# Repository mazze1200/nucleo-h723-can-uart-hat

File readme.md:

# CAN and UART hat for STM32 Nucleo H723ZG eval board

# FTDI Sub-D 
Pin 1 = TXD / PIN16
Pin 6 = RXD / PIN17
Pin 3 = GND

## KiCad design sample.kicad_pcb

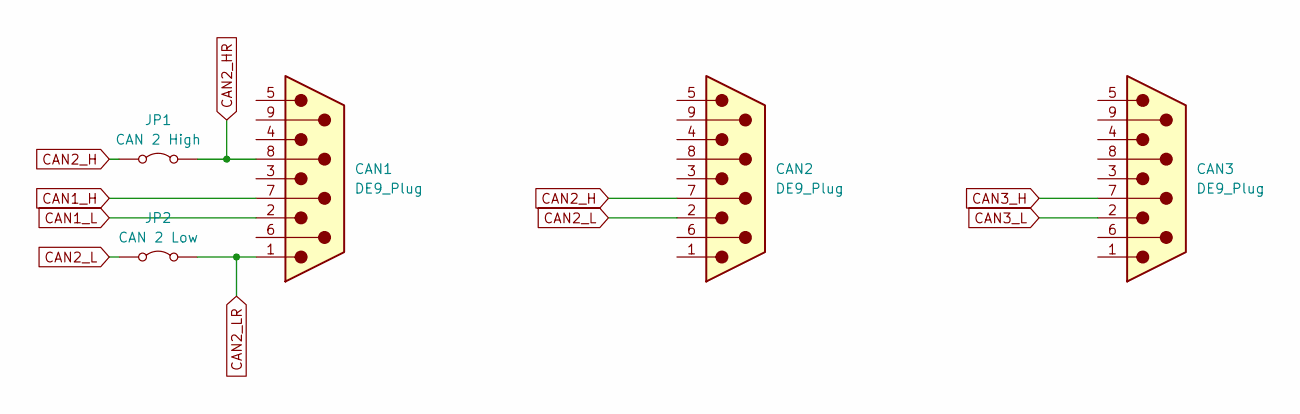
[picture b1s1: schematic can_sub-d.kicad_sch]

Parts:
CAN1, CAN2, CAN3: DE9_Plug; DSUB-9_Female_Horizontal_P2.77x2.54mm_EdgePinOffset9.40mm
JP1: CAN 2 High; TestPoint_2Pads_Pitch2.54mm_Drill0.8mm
JP2: CAN 2 Low; TestPoint_2Pads_Pitch2.54mm_Drill0.8mm

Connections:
CAN1_H: CAN1.7; also elsewhere on the board
CAN1_L: CAN1.2; also elsewhere on the board
CAN2_H: CAN2.7, JP1.1 (A); also elsewhere on the board
CAN2_HR: CAN1.8, JP1.2 (B)
CAN2_L: CAN2.2, JP2.1 (A); also elsewhere on the board
CAN2_LR: CAN1.1, JP2.2 (B)
CAN3_H: CAN3.7; also elsewhere on the board
CAN3_L: CAN3.2; also elsewhere on the board

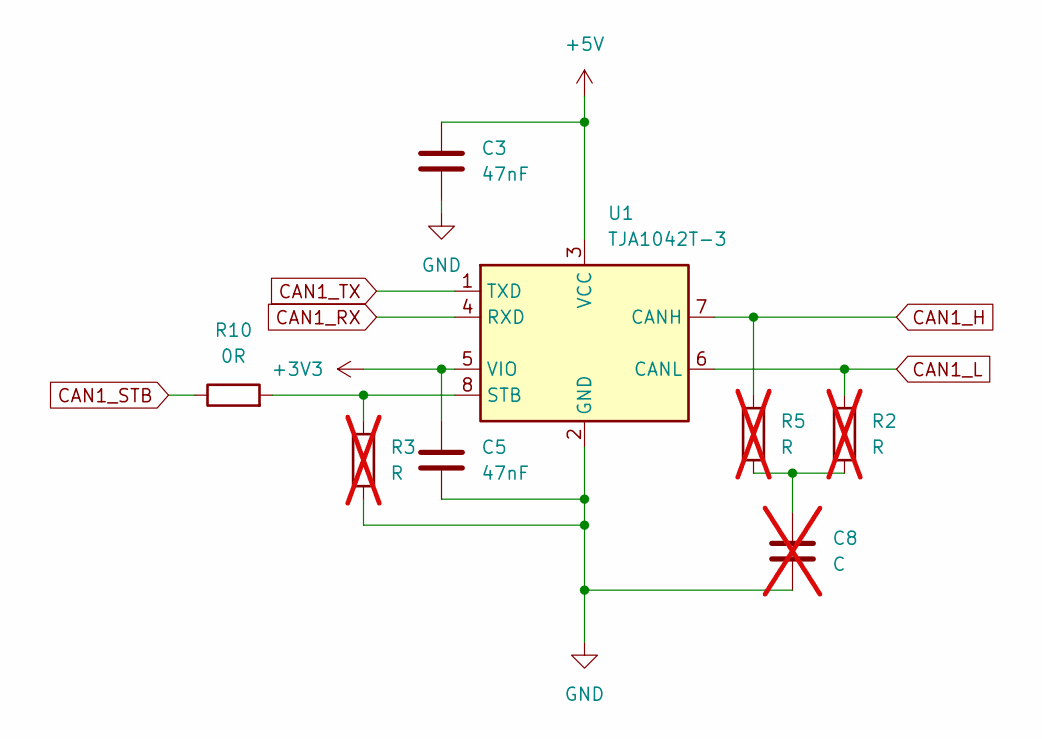
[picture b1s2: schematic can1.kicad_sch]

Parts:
C3, C5: 47nF; C_1206_3216Metric_Pad1.33x1.80mm_HandSolder
C8: C; C_1206_3216Metric_Pad1.33x1.80mm_HandSolder; not fitted
R2, R3, R5: R; R_1206_3216Metric_Pad1.30x1.75mm_HandSolder; not fitted
R10: 0R; R_1206_3216Metric_Pad1.30x1.75mm_HandSolder
U1: TJA1042T-3; SOIC-8_3.9x4.9mm_P1.27mm

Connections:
+3V3: C5.1, U1.5 (VIO); also elsewhere on the board
+5V: C3.1, U1.3 (VCC); also elsewhere on the board
CAN1_H: R5.1, U1.7 (CANH); also elsewhere on the board
CAN1_L: R2.1, U1.6 (CANL); also elsewhere on the board
CAN1_RX: U1.4 (RXD); also elsewhere on the board
CAN1_STB: R10.1; also elsewhere on the board
CAN1_TX: U1.1 (TXD); also elsewhere on the board
GND: C3.2, C5.2, C8.2, R3.2, U1.2 (GND); also elsewhere on the board
unnamed: C8.1, R2.2, R5.2
unnamed: R3.1, R10.2, U1.8 (STB)

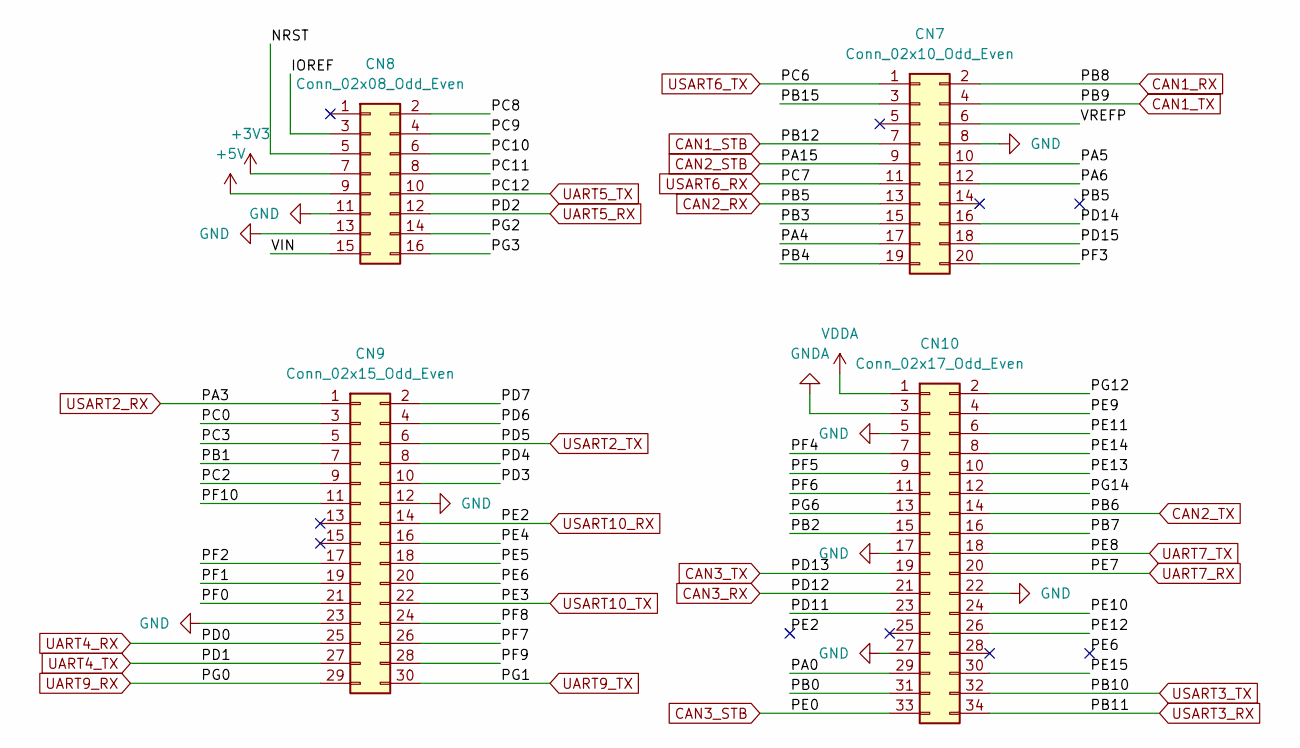
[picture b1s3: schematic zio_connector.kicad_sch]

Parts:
CN7: Conn_02x10_Odd_Even; PinHeader_2x10_P2.54mm_Vertical
CN8: Conn_02x08_Odd_Even; PinHeader_2x08_P2.54mm_Vertical
CN9: Conn_02x15_Odd_Even; PinHeader_2x15_P2.54mm_Vertical
CN10: Conn_02x17_Odd_Even; PinHeader_2x17_P2.54mm_Vertical

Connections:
+3V3: CN8.7; also elsewhere on the board
+5V: CN8.9; also elsewhere on the board
/ZIO Connector/IOREF: CN8.3
/ZIO Connector/NRST: CN8.5
/ZIO Connector/PA0: CN10.29
/ZIO Connector/PA4: CN7.17
/ZIO Connector/PA5: CN7.10
/ZIO Connector/PA6: CN7.12
/ZIO Connector/PB0: CN10.31
/ZIO Connector/PB1: CN9.7
/ZIO Connector/PB2: CN10.15
/ZIO Connector/PB3: CN7.15
/ZIO Connector/PB4: CN7.19
/ZIO Connector/PB7: CN10.16
/ZIO Connector/PB15: CN7.3
/ZIO Connector/PC0: CN9.3
/ZIO Connector/PC2: CN9.9
/ZIO Connector/PC3: CN9.5
/ZIO Connector/PC8: CN8.2
/ZIO Connector/PC9: CN8.4
/ZIO Connector/PC10: CN8.6
/ZIO Connector/PC11: CN8.8
/ZIO Connector/PD3: CN9.10
/ZIO Connector/PD4: CN9.8
/ZIO Connector/PD6: CN9.4
/ZIO Connector/PD7: CN9.2
/ZIO Connector/PD11: CN10.23
/ZIO Connector/PD14: CN7.16
/ZIO Connector/PD15: CN7.18
/ZIO Connector/PE4: CN9.16
/ZIO Connector/PE5: CN9.18
/ZIO Connector/PE6: CN9.20
/ZIO Connector/PE9: CN10.4
/ZIO Connector/PE10: CN10.24
/ZIO Connector/PE11: CN10.6
/ZIO Connector/PE12: CN10.26
/ZIO Connector/PE13: CN10.10
/ZIO Connector/PE14: CN10.8
/ZIO Connector/PE15: CN10.30
/ZIO Connector/PF0: CN9.21
/ZIO Connector/PF1: CN9.19
/ZIO Connector/PF2: CN9.17
/ZIO Connector/PF3: CN7.20
/ZIO Connector/PF4: CN10.7
/ZIO Connector/PF5: CN10.9
/ZIO Connector/PF6: CN10.11
/ZIO Connector/PF7: CN9.26
/ZIO Connector/PF8: CN9.24
/ZIO Connector/PF9: CN9.28
/ZIO Connector/PF10: CN9.11
/ZIO Connector/PG2: CN8.14
/ZIO Connector/PG3: CN8.16
/ZIO Connector/PG6: CN10.13
/ZIO Connector/PG12: CN10.2
/ZIO Connector/PG14: CN10.12
/ZIO Connector/VIN: CN8.15
/ZIO Connector/VREFP: CN7.6
CAN1_RX: CN7.2; also elsewhere on the board
CAN1_STB: CN7.7; also elsewhere on the board
CAN1_TX: CN7.4; also elsewhere on the board
CAN2_RX: CN7.13; also elsewhere on the board
CAN2_STB: CN7.9; also elsewhere on the board
CAN2_TX: CN10.14; also elsewhere on the board
CAN3_RX: CN10.21; also elsewhere on the board
CAN3_STB: CN10.33; also elsewhere on the board
CAN3_TX: CN10.19; also elsewhere on the board
GND: CN7.8, CN8.11, CN8.13, CN9.12, CN9.23, CN10.5, CN10.17, CN10.22, CN10.27; also elsewhere on the board
GNDA: CN10.3
UART4_RX: CN9.25; also elsewhere on the board
UART4_TX: CN9.27; also elsewhere on the board
UART5_RX: CN8.12; also elsewhere on the board
UART5_TX: CN8.10; also elsewhere on the board
UART7_RX: CN10.20; also elsewhere on the board
UART7_TX: CN10.18; also elsewhere on the board
UART9_RX: CN9.29; also elsewhere on the board
UART9_TX: CN9.30; also elsewhere on the board
USART2_RX: CN9.1; also elsewhere on the board
USART2_TX: CN9.6; also elsewhere on the board
USART3_RX: CN10.34; also elsewhere on the board
USART3_TX: CN10.32; also elsewhere on the board
USART6_RX: CN7.11; also elsewhere on the board
USART6_TX: CN7.1; also elsewhere on the board
USART10_RX: CN9.14; also elsewhere on the board
USART10_TX: CN9.22; also elsewhere on the board
VDDA: CN10.1

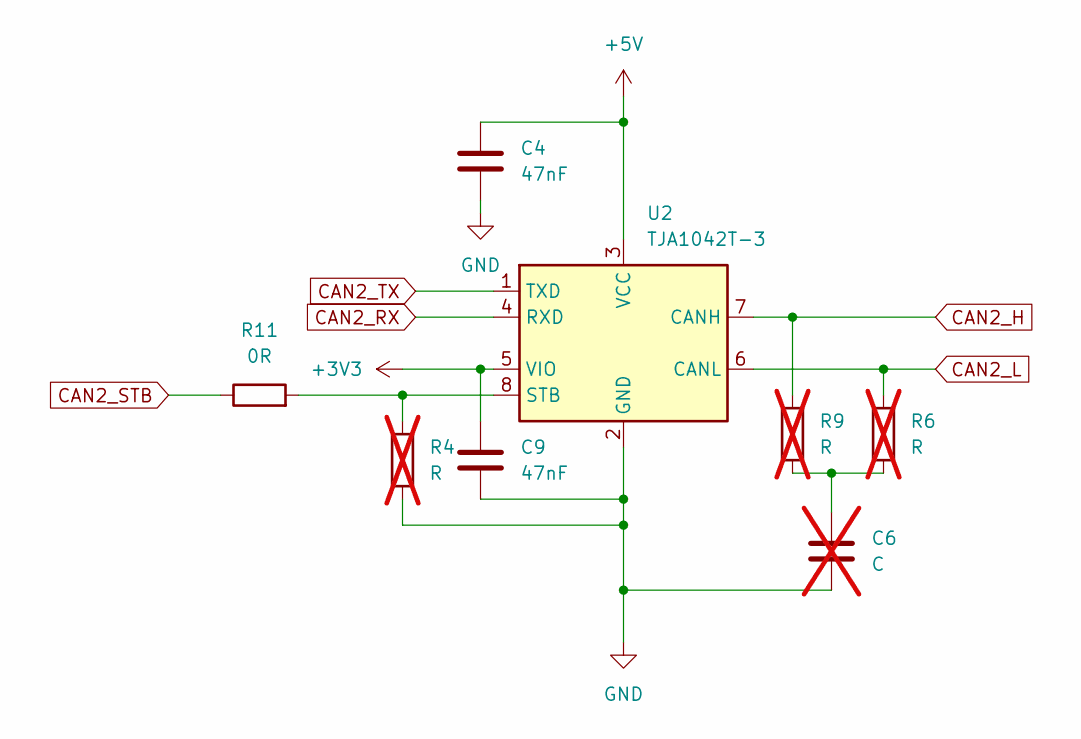
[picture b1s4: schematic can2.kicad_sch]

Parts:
C4, C9: 47nF; C_1206_3216Metric_Pad1.33x1.80mm_HandSolder
C6: C; C_1206_3216Metric_Pad1.33x1.80mm_HandSolder; not fitted
R4, R6, R9: R; R_1206_3216Metric_Pad1.30x1.75mm_HandSolder; not fitted
R11: 0R; R_1206_3216Metric_Pad1.30x1.75mm_HandSolder
U2: TJA1042T-3; SOIC-8_3.9x4.9mm_P1.27mm

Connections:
+3V3: C9.1, U2.5 (VIO); also elsewhere on the board
+5V: C4.1, U2.3 (VCC); also elsewhere on the board
CAN2_H: R9.1, U2.7 (CANH); also elsewhere on the board
CAN2_L: R6.1, U2.6 (CANL); also elsewhere on the board
CAN2_RX: U2.4 (RXD); also elsewhere on the board
CAN2_STB: R11.1; also elsewhere on the board
CAN2_TX: U2.1 (TXD); also elsewhere on the board
GND: C4.2, C6.2, C9.2, R4.2, U2.2 (GND); also elsewhere on the board
unnamed: C6.1, R6.2, R9.2
unnamed: R4.1, R11.2, U2.8 (STB)

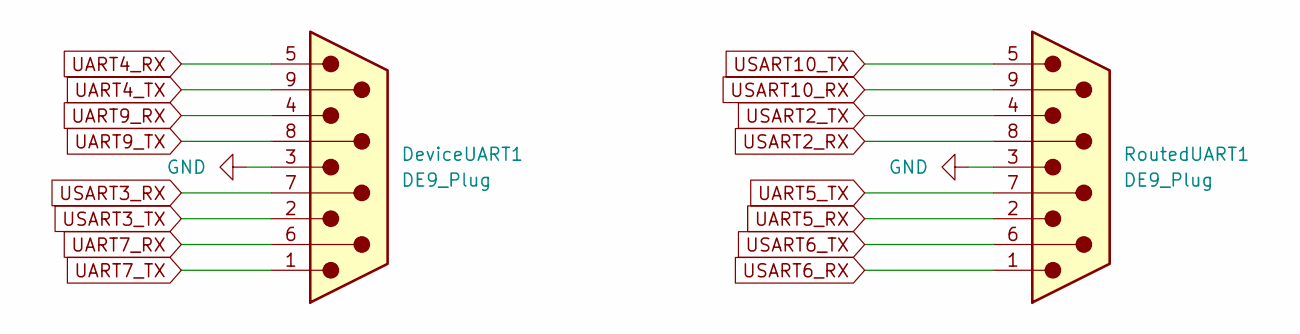
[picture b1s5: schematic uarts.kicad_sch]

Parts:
DeviceUART1: DE9_Plug; DSUB-9_Female_Horizontal_P2.77x2.54mm_EdgePinOffset9.40mm
RoutedUART1: DE9_Plug; DSUB-9_Male_Horizontal_P2.77x2.54mm_EdgePinOffset9.40mm

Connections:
GND: DeviceUART1.3, RoutedUART1.3; also elsewhere on the board
UART4_RX: DeviceUART1.5; also elsewhere on the board
UART4_TX: DeviceUART1.9; also elsewhere on the board
UART5_RX: RoutedUART1.2; also elsewhere on the board
UART5_TX: RoutedUART1.7; also elsewhere on the board
UART7_RX: DeviceUART1.6; also elsewhere on the board
UART7_TX: DeviceUART1.1; also elsewhere on the board
UART9_RX: DeviceUART1.4; also elsewhere on the board
UART9_TX: DeviceUART1.8; also elsewhere on the board
USART2_RX: RoutedUART1.8; also elsewhere on the board
USART2_TX: RoutedUART1.4; also elsewhere on the board
USART3_RX: DeviceUART1.7; also elsewhere on the board
USART3_TX: DeviceUART1.2; also elsewhere on the board
USART6_RX: RoutedUART1.1; also elsewhere on the board
USART6_TX: RoutedUART1.6; also elsewhere on the board
USART10_RX: RoutedUART1.9; also elsewhere on the board
USART10_TX: RoutedUART1.5; also elsewhere on the board

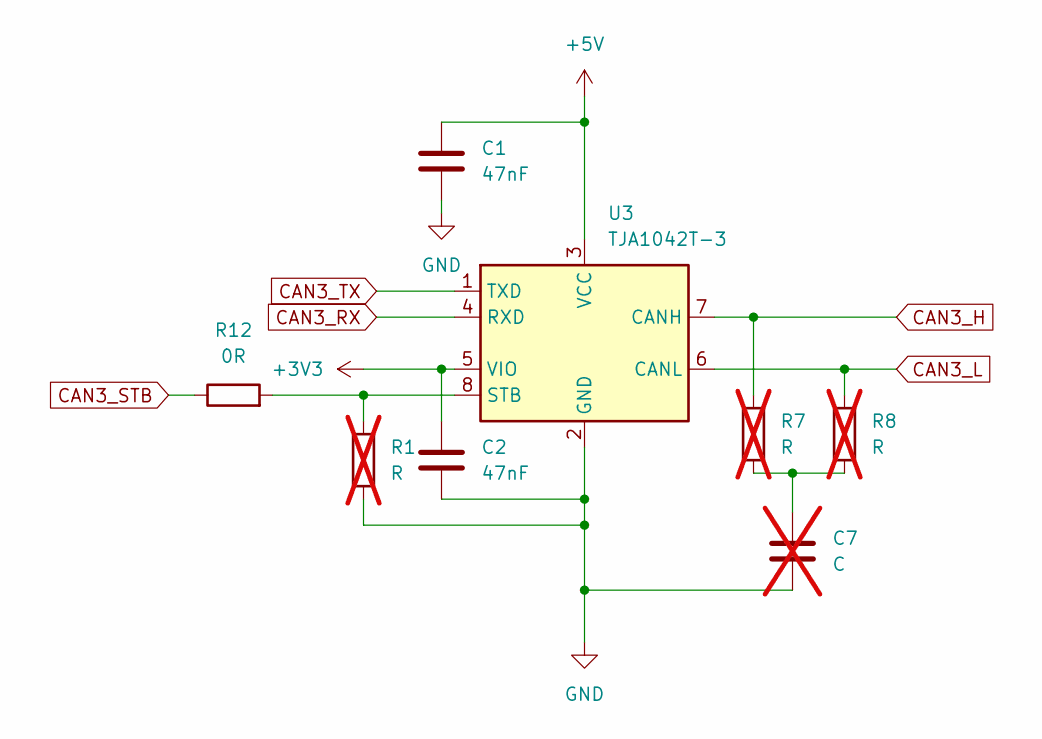
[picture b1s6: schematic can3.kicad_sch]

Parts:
C1, C2: 47nF; C_1206_3216Metric_Pad1.33x1.80mm_HandSolder
C7: C; C_1206_3216Metric_Pad1.33x1.80mm_HandSolder; not fitted
R1, R7, R8: R; R_1206_3216Metric_Pad1.30x1.75mm_HandSolder; not fitted
R12: 0R; R_1206_3216Metric_Pad1.30x1.75mm_HandSolder
U3: TJA1042T-3; SOIC-8_3.9x4.9mm_P1.27mm

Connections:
+3V3: C2.1, U3.5 (VIO); also elsewhere on the board
+5V: C1.1, U3.3 (VCC); also elsewhere on the board
CAN3_H: R7.1, U3.7 (CANH); also elsewhere on the board
CAN3_L: R8.1, U3.6 (CANL); also elsewhere on the board
CAN3_RX: U3.4 (RXD); also elsewhere on the board
CAN3_STB: R12.1; also elsewhere on the board
CAN3_TX: U3.1 (TXD); also elsewhere on the board
GND: C1.2, C2.2, C7.2, R1.2, U3.2 (GND); also elsewhere on the board
unnamed: C7.1, R7.2, R8.2
unnamed: R1.1, R12.2, U3.8 (STB)

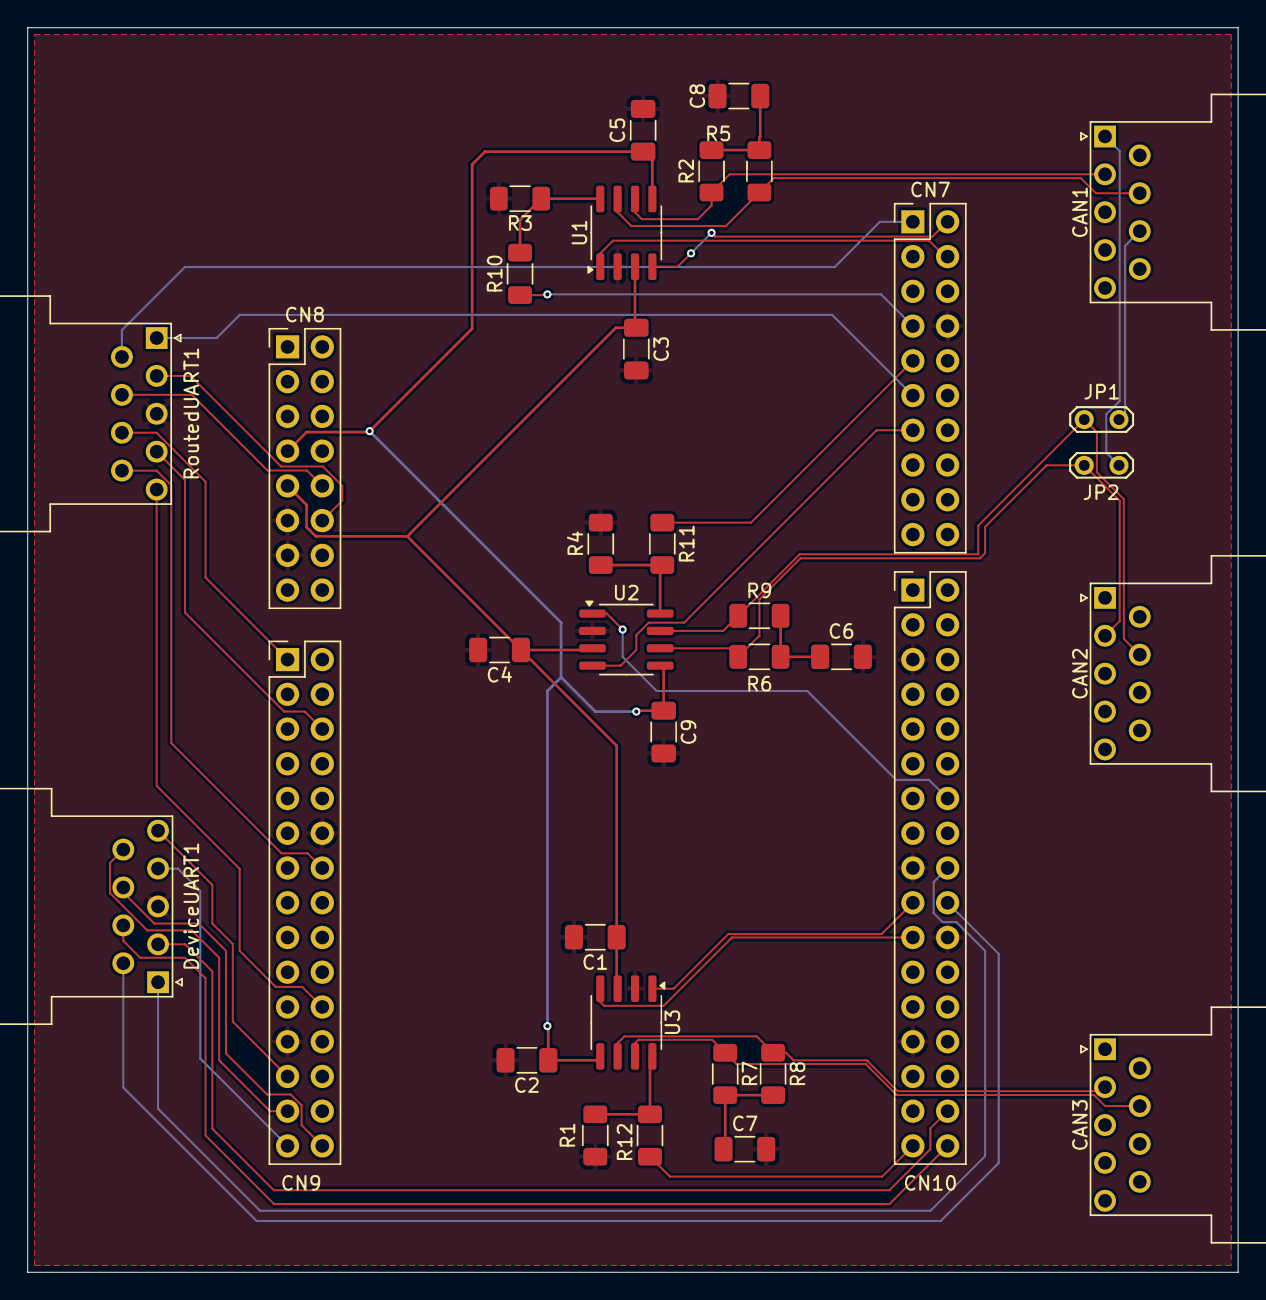
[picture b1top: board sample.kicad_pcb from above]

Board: 2 copper layers, 88.5 x 91.0 mm, 35 parts (0 on the bottom side), 42 nets.

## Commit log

2024-05-31 add ZIO connectiors
2024-05-31 add notes with position of CN7, CN8, CN9, CN10
2024-05-31 split into hirachical pages
2024-05-31 finalize CAN1
2024-05-31 add CAN2 and CAN3
2024-05-31 fix double numbers
2024-05-31 connect CANs to ZIO
2024-05-31 move connectors to zio_connectors
2024-05-31 add CAN Sub-D connectors
2024-05-31 rename jumpers
2024-05-31 list of UART pins
2024-05-31 add mapping for ADCs
2024-05-31 add CAN STB pins
2024-05-31 route uarts
2024-05-31 place CNs correctly (?)
2024-05-31 fix some placement
2024-06-01 readdress CAN pins for better routing
2024-06-01 placements
2024-06-01 adapt Signal net rule
2024-06-01 uarts routed
2024-06-01 some connection for CAN1
2024-06-01 CAN1 finished
2024-06-01 All nets conected except GND, +3V3, +5V
2024-06-01 All nets conected except GND
2024-06-01 add copper fill
2024-06-01 small fixes
2024-06-02 add gerber files which where ordered
2024-06-02 rename
